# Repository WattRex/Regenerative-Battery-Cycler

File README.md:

<div style="display: flex; align-items: center;">
  
    <h1>TowerPower, a regenerative battery cycler</h1>
</div>

## The project

### Introduction

<p align="justify">The regenerative battery cycler is an innovative project aimed at providing a cost-effective, precise, and easy-to-build solution for testing batteries. It caters to a wide range of individuals and organizations, including researchers, R&D institutions, second life markets, and DIY energy enthusiasts who are interested in battery testing. The roots of this project trace back to 2018 when Pablo Pastor embarked on his PhD journey, focusing on machine learning for second life  batteries. During his research, he encountered a significant challenge: there was a scarcity of open-source aging databases. Determined to address this issue, Pastor and his team proposed creating  their own databases. However, due to budget constraints, they had to find an affordable solution. The initial concepts were developed within the Group of Power Electronics and Microelectronics (GEPM). </p>

<p align="justify">Over time, these concepts evolved, prioritizing three key factors: cost, simplicity, and precision. In 2021, a group of power electronic engineers, software developers, and energy sector experts from the PTI-Transener platform, operated by the Spanish National Research Council (CSIC) joined forces to propel the project forward. The team is currently focused on adapting the regenerative battery cycler to accommodate various battery chemistries, ensuring its versatility and applicability across different industries. </p>

<p align="justify">As part of the Pastor's thesis and the PTI-Transener project, we have made the decision to share the regenerative battery cycler as an open-source product. This approach aims to support other researchers and energy enthusiasts by providing them with a low-budget option for their studies. Additionally, we emphasize a structured development process, ensuring transparency and accountability. All steps, design decisions, and technical details, from initial system requirements to final schematics, bill of materials (BOM), and embedded code are openly shared, enabling others to replicate and build upon our work. </p>

<p align="justify">By providing a cost-effective, accessible, and open-source regenerative battery cycler: TowerPower. We aim to facilitate battery testing and contribute to the advancement of research and development in the field of energy storage. </p>

### Working principle

<p align="justify">TowerPower stands out as a bidirectional system, capable of both charging and discharging cells. This versatility allows for comprehensive testing and evaluation of batteries under various operating conditions. Moreover, unlike many low-end cyclers that dissipate energy as heat, TowerPower minimizes energy loss during the cycling process (taking into account system efficiency). By efficiently transferring energy from one battery to  another, this system proves to be significantly more economical to operate compared to chargers that rely on resistive discharging methods, which result in energy wastage. TowerPower optimizes energy utilization, ensuring a cost-effective and sustainable solution for battery testing and research. </p>

<p align="justify">TowerPower operates based on a DC-DC synchronous buck power converter, enabling energy transfer from a higher voltage input source to a lower voltage output where the device under test (DUT), such as a cell, is connected. The use of a buck converter allows control on the low voltage side while lacking control on the high voltage side, as seen in buck-boost converters. Moreover, the synchronous architecture of the converter enables bidirectional current flow, facilitating both charging and discharging processes. </p>

<p align="justify">To simplify the electronics and eliminate the need for energy transfer to the grid, the system uses an energy accumulator on the high voltage side. This can be achieved using a 12 V car battery or a stack of lithium cells with a voltage exceeding 5.5V. In our lab, a 6V high-capacity deep cycle gel Pb battery is used, allowing multiple cyclers to be connected in parallel. </p>

<p align="justify">The control of TowerPower is accomplished through a CAN bus interface, providing seamless communication between the cycler and the external controller. Additionally, a dedicated control software has been developed and released, enabling users to command test cycles and gather results effectively.  <a href="https://github.com/WattRex/Battery-Cyclers-Controler">Repo here</a>!</p>

<p align="justify">In this particular version of the cycler, a low-cost power device with integrated driver and transistors has been chosen. This decision not only reduces costs but also enhances the miniaturization of the product. Furthermore, the switching frequency of the converter has been increased, resulting in a smaller coil size, contributing to the overall cost and compactness of the system. </p>

### Acknowledgements
<p align="justify">This research has been developed within the CSIC Interdisciplinary Thematic Platform (PTI+) Transición Energética Sostenible+ (PTI-TRANSENER+) as part of the CSIC program for the Spanish Recovery, Transformation and Resilience Plan funded by the Recovery and Resilience Facility of the European Union, established by the Regulation (EU) 2020/2094. Funding from the Spanish Ministry of Science and Innovation under project MAFALDA (PID2021-126001OB-C32) is also acknowledged. </p>

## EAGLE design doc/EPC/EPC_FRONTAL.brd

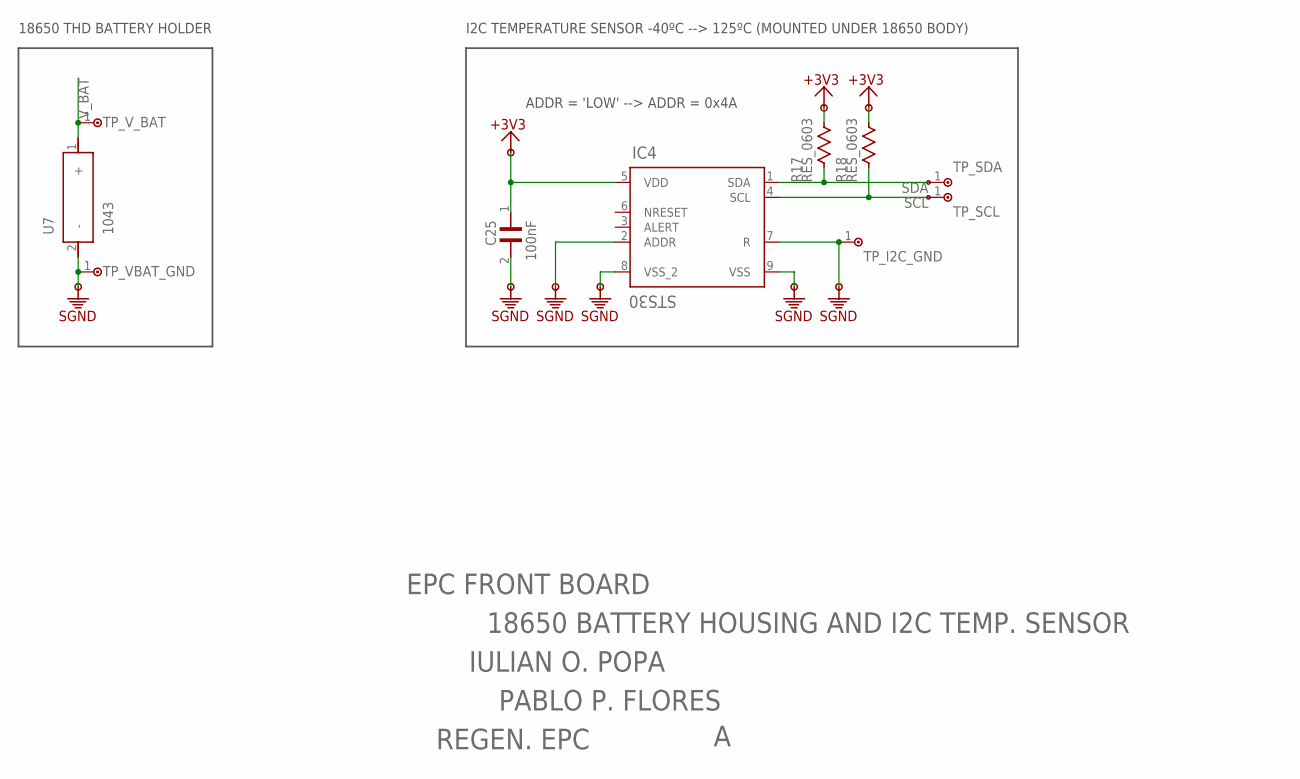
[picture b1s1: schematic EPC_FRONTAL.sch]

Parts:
C25: 100nF; CAP_0603
IC4: STS30; DFN
R17, R18: RES_0603
TP_I2C_GND: TP_S2751-46R
TP_SCL: TP_S2751-46R
TP_SDA: TP_S2751-46R
TP_VBAT_GND: TP_S2751-46R
TP_V_BAT: TP_S2751-46R
U7: 1043

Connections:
+3V3: C25.1, IC4.5 (VDD), R17.2, R18.2
SCL: IC4.4 (SCL), R18.1, TP_SCL.1
SDA: IC4.1 (SDA), R17.1, TP_SDA.1
SGND: C25.2, IC4.2 (ADDR), IC4.7 (R), IC4.8 (VSS_2), IC4.9 (VSS), TP_I2C_GND.1, TP_VBAT_GND.1, U7.2 (-)
V_BAT: TP_V_BAT.1, U7.1 (+)

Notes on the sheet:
ADDR = 'LOW' --> ADDR = 0x4A
18650 THD BATTERY HOLDER
I2C TEMPERATURE SENSOR -40ºC --> 125ºC (MOUNTED UNDER 18650 BODY)
EPC FRONT BOARD
18650 BATTERY HOUSING AND I2C TEMP. SENSOR
IULIAN O. POPA
PABLO P. FLORES
REGEN. EPC

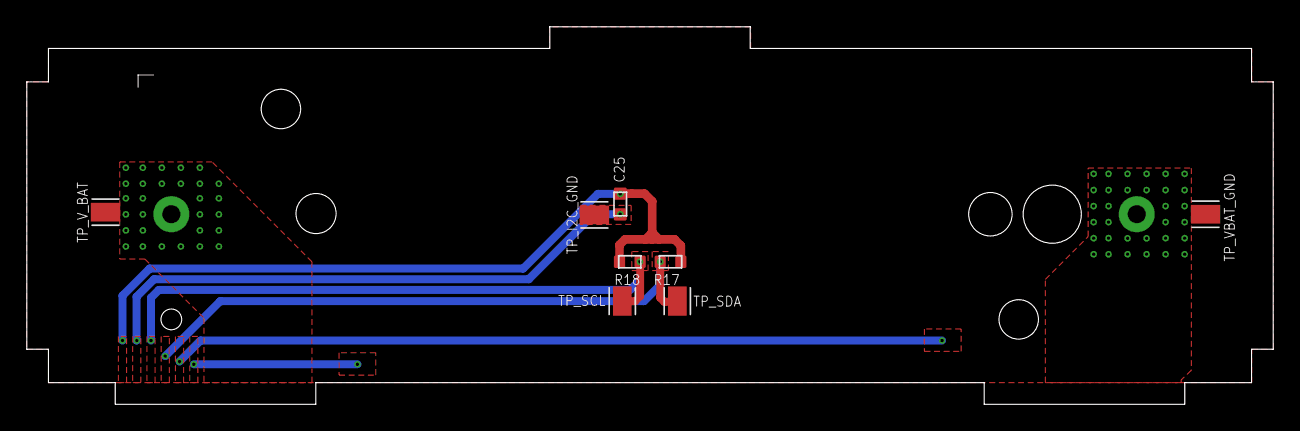
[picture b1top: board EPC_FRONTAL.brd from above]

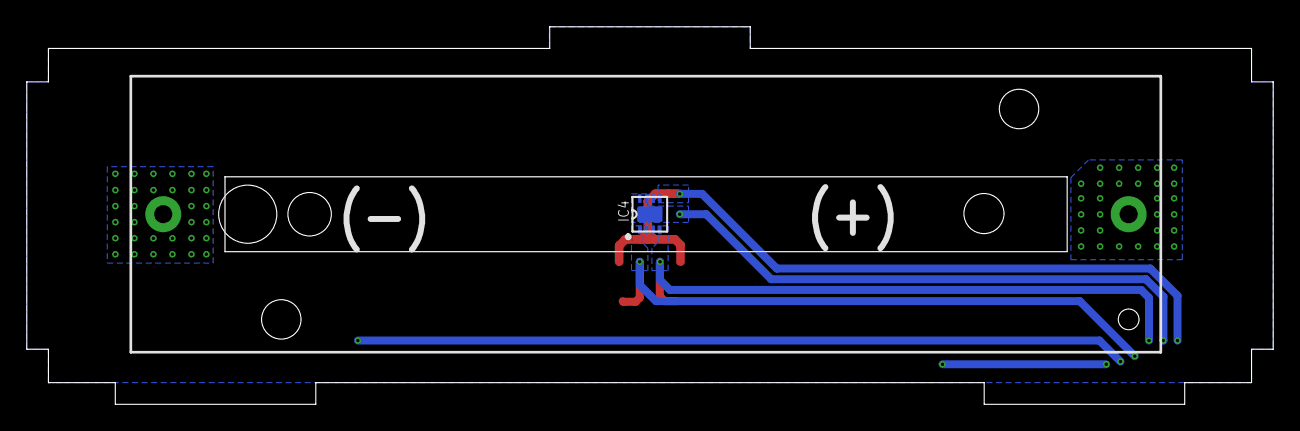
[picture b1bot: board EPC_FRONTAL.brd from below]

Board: 4 copper layers, 93.2 x 28.2 mm, 10 parts (2 on the bottom side), 5 nets.

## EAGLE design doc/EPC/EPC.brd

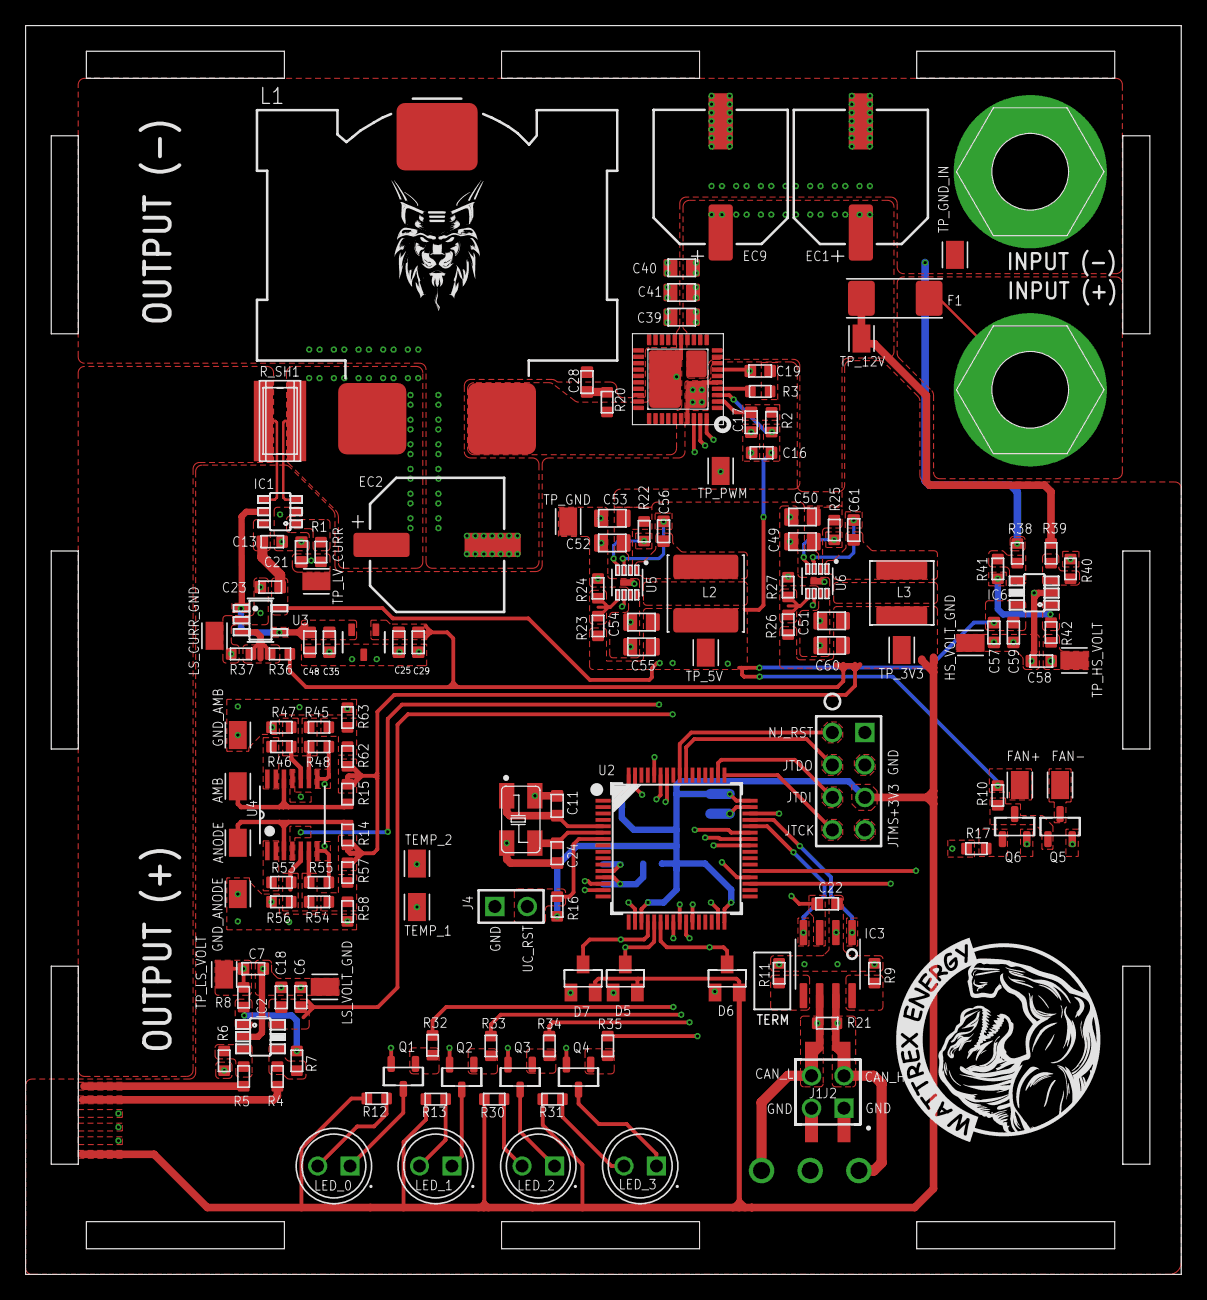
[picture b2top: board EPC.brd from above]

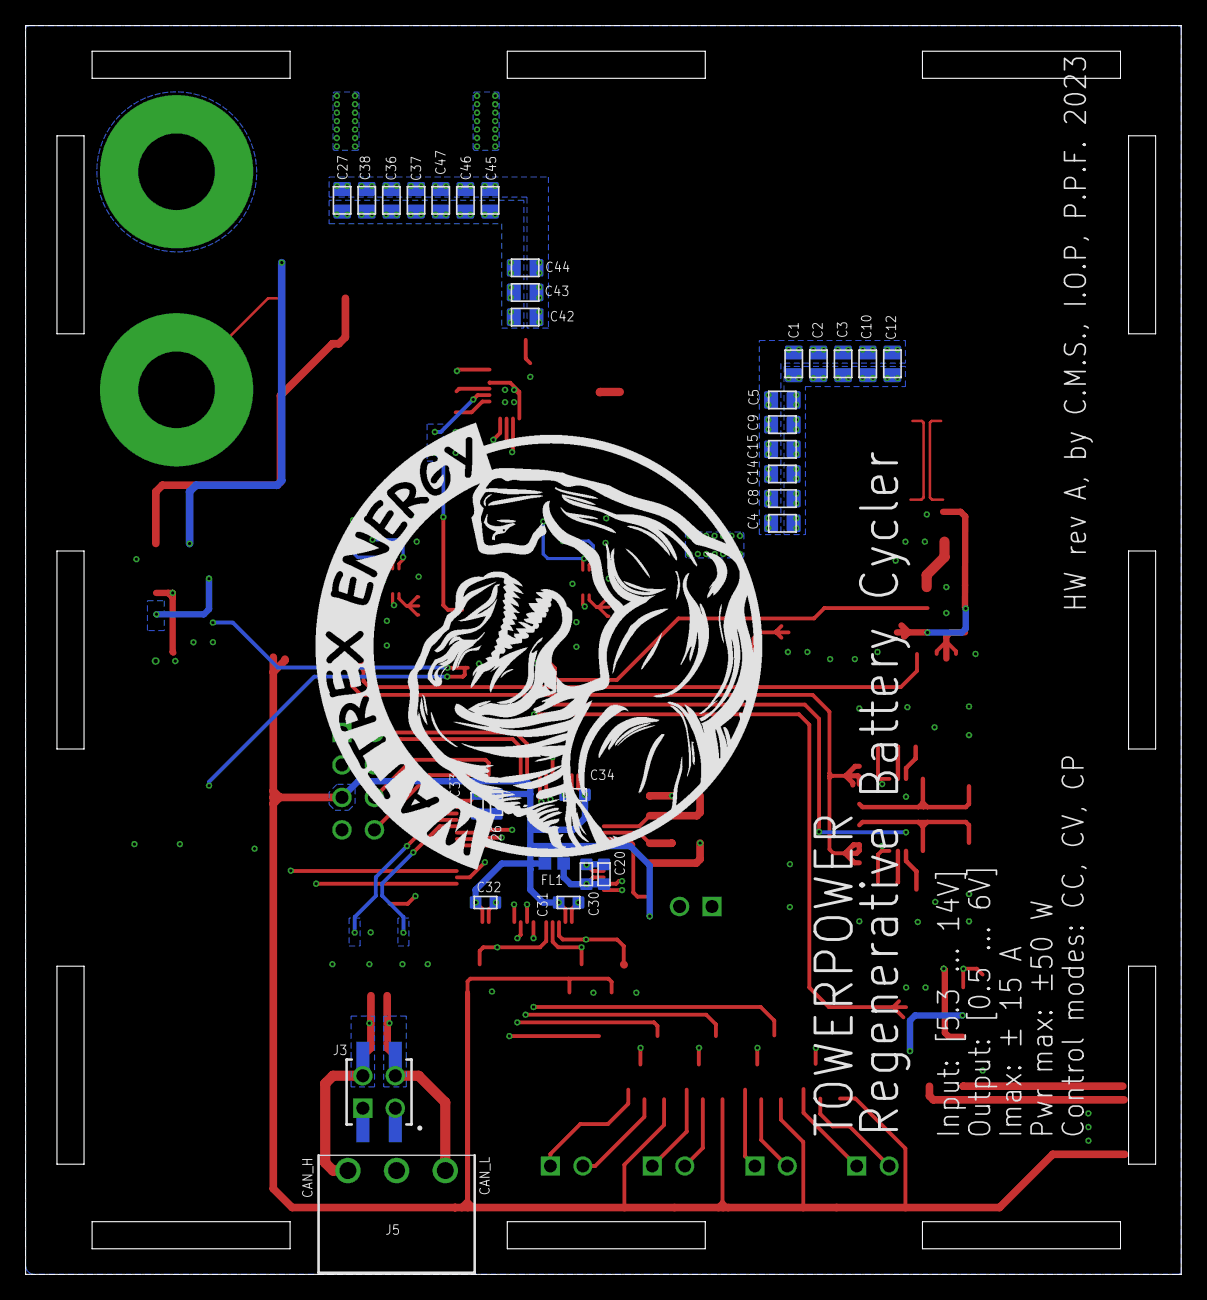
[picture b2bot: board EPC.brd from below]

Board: 4 copper layers, 90.5 x 97.8 mm, 174 parts (31 on the bottom side), 84 nets.

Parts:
AMB: TP_S2751-46R
ANODE: TP_S2751-46R
C1, C2, C3, C4, C5, C8, C9, C10, C12, C14, C15, C27, C36, C37, C38, C39, C40, C41, C42, C43, C44, C45, C46, C47, C51, C54, C55, C60: 22uF / 0805; CAP_0805
C6, C13, C19, C20, C22, C23, C25, C29, C31, C32, C33, C34, C35, C48, C57: 100nF; CAP_0603
C7, C21, C58: Cf; CAP_0603
C11, C24: 22pF; CAP_0603
C16, C17, C18, C30, C59: 1uF; CAP_0603
C26: 4.7uF; CAP_0603
C28: Csnb; CAP_0603
C49, C50, C52, C53: 10uF / 0805; CAP_0805
C56, C61: 10nF; CAP_0603
D5, D6, D7: BAT54S
EC1, EC2, EC9: 100uF; WCAP-PSLC_10X12.4(DXL)
F1: FUSE_SF-2410FP010T-2FUSE_SF_6P1X2P6_BRN-M; FUSE_SF-2410FP010T-2
FAN+: TP_S2751-46R
FAN-: TP_S2751-46R
FL1: 600Ohm/100MHz; FERR_0603_600OHM
GND_AMB: TP_S2751-46R
GND_ANODE: TP_S2751-46R
HS_VOLT_GND: TP_S2751-46R
IC1: INA181A2IDBVTDBV0006A_L; SOT-23-6
IC2, IC6: TSV7721ILT; SOT-23-5
IC3: MAX3059ASA
IC4: MAX6018AEUR16+T21-0051H_MXM-L; SOT-23
J1, J3: SSM-102-T-DV
J2: TSW-125-19-T-D
J4: 2_POS_HEADER
J5: CONN_3_POS
JTAG1: JTAG
L1: PQ2617BHA-150K
L2: VLS6045EX-220M; IND_VLS6045EX-220M
L3: VLS5045EX-150M; IND_VLS5045EX-150M
LED_0, LED_1, LED_2, LED_3: WP7113ID; LED_WP7113ID
LS_CURR_GND: TP_S2751-46R
LS_VOLT_GND: TP_S2751-46R
Q1, Q2, Q3, Q4, Q6: NX7002AK_215
Q5: PJA3430; NX7002AK_215
R1, R8, R42: Rf; RES_0603
R2: 10Ω; RES_0603
R3: 2Ω; RES_0603
R4, R5: 150kΩ; RES_0603
R6, R7: 82kΩ; RES_0603
R9: 51kΩ; RES_0603
R10, R16, R36, R37: 10kΩ; RES_0603
R11: R0; RES_0603
R12, R13, R17, R30, R31, R32, R33, R34, R35: 1kΩ; RES_0603
R14, R15: 3.32kΩ; RES_0603
R19: FCSL64R002GERRES_FCSL64_OHM-M; RES_FCSL64_OHM-M
R20: Rsnb; RES_0603
R21: 120Ω; RES_0603
R22, R25, R38, R39: 100kΩ; RES_0603
R23: 120kΩ; RES_0603
R24, R40, R41: 22kΩ; RES_0603
R26, R45, R46, R53, R54: 110kΩ; RES_0603
R27: 36kΩ; RES_0603
R47, R48, R55, R56: 140kΩ; RES_0603
R57, R62: 16.5kΩ; RES_0603
R58, R63: 2.2kΩ; RES_0603
R_SH1: WSL10203L000FEA; RES1020
SP1, SP2: SPACER_M6X25MM
TEMP_1, TEMP_2: TP_S2751-46R
TP_3V3, TP_5V, TP_12V: TP_S2751-46R
TP_GND: TP_S2751-46R
TP_GND_IN: TP_S2751-46R
TP_HS_VOLT: TP_S2751-46R
TP_LS_VOLT: TP_S2751-46R
TP_LV_CURR: TP_S2751-46R
TP_PWM: TP_S2751-46R
U1: FDMF6820C
U2: STM32F334R8T6; STM32F334R8
U3: TL071HIDBVR
U4: LM224APT
U5, U6: RT7251AZQW; WDFN-8L
XTAL1: MCSJK-7I-8.00-10-30-60-B-30

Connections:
+3V3: C25.1, C26.1, C29.1, C31.1, C32.1, C33.1, C34.1, C51.1, C60.1, D5.K, D6.K, D7.K, FL1.2, IC4.1, JTAG1.06, L3.2, R12.2, R13.2, R14.1, R15.1, R16.2, R26.2, R30.2, R31.2, R36.2, R57.2, R62.2, TP_3V3.1, U2.19, U2.32, U2.48, U2.64
+5V: C6.1, C13.1, C16.1, C18.1, C22.1, C23.1, C54.1, C55.1, C57.1, C59.1, FAN+.1, IC1.6, IC2.5, IC3.3, IC6.5, L2.2, R2.2, R10.2, R23.2, TP_5V.1, U1.3, U3.5, U4.4
+12V: C27.1, C36.1, C37.1, C38.1, C39.1, C40.1, C41.1, C42.1, C43.1, C44.1, C45.1, C46.1, C47.1, C49.1, C50.1, C52.1, C53.1, EC1.1, EC9.1, F1.2, R22.1, R25.1, R39.1, TP_12V.1, U1.9, U1.10, U1.11, U1.12, U1.13, U1.14, U1.42, U5.2, U6.2
CAN_H: IC3.7, J1.02, J2.02, J3.04, J5.1, R21.2
CAN_L: IC3.6, J1.04, J2.04, J3.02, J5.3, R21.1
CAN_RX: IC3.4, U2.44
CAN_TX: IC3.1, U2.45
EXT_TEMP_1: R55.1, TEMP_1.1, U2.15, U4.7
EXT_TEMP_2: R48.2, TEMP_2.1, U2.14, U4.8
FAN_CTRL: R17.1, U2.37
HS_VOLT: C58.1, D6.AK, R42.2, TP_HS_VOLT.1, U2.22
LED0: R32.1, U2.24
LED1: R33.1, U2.25
LED2: R34.1, U2.26
LED3: R35.1, U2.27
LS_CURR: C21.1, D7.AK, R1.2, TP_LV_CURR.1, U2.20
LS_VOLT: C7.1, D5.AK, R8.2, TP_LS_VOLT.1, U2.21
unnamed: IC1.1, R1.1
unnamed: C19.1, R3.2
unnamed: R3.1, U1.4
unnamed: IC2.4, R4.2, R7.1
unnamed: IC2.3, R5.2, R6.2
unnamed: IC2.1, R7.2, R8.1
unnamed: C28.1, R20.2
unnamed: Q5.1, Q6.3, R10.1
unnamed: FAN-.1, Q5.3
unnamed: IC6.4, R38.2, R41.1
unnamed: IC6.3, R39.2, R40.2
unnamed: IC6.1, R41.2, R42.1
unnamed: Q6.1, R17.2
unnamed: R25.2, U6.4
unnamed: C61.1, L3.1, U6.1
unnamed: R26.1, R27.2, U6.5
unnamed: C61.2, U6.3
unnamed: R22.2, U5.4
unnamed: C56.1, L2.1, U5.1
unnamed: R23.1, R24.2, U5.5
unnamed: C56.2, U5.3
unnamed: R45.1, R48.1, U4.9
unnamed: IC3.8, R9.2
unnamed: IC3.5, R11.2
unnamed: LED_0.A, R12.1
unnamed: LED_0.C, Q1.3
unnamed: LED_1.C, Q2.3
unnamed: LED_1.A, R13.1
unnamed: LED_2.A, R30.1
unnamed: LED_2.C, Q3.3
unnamed: LED_3.C, Q4.3
unnamed: LED_3.A, R31.1
unnamed: Q1.1, R32.2
unnamed: R46.2, R47.2, U4.10
unnamed: Q2.1, R33.2
unnamed: Q3.1, R34.2
unnamed: Q4.1, R35.2
unnamed: R36.1, R37.2, U3.3
unnamed: F1.1, SP1.P$1
unnamed: R53.1, R56.1, U4.5
unnamed: R54.2, R55.2, U4.6
unnamed: R54.1, R57.1, R58.2
unnamed: R45.2, R62.1, R63.2
NTC_1: ANODE.1, R14.2, U4.3
NTC_2: AMB.1, R15.2, U4.12
OUT_DISABLE: U1.39, U2.42
PWM_OUT: TP_PWM.1, U1.40, U2.41
RCC_OSC_IN: C11.1, U2.5, XTAL1.#1
RCC_OSC_OUT: C24.1, U2.6, XTAL1.#3
REF_1V65: C35.1, C48.1, IC1.5, IC4.2, U3.1, U3.4
SGND: C1.2, C2.2, C3.2, C4.2, C5.2, C6.2, C7.2, C8.2, C9.2, C10.2, C11.2, C12.2, C13.2, C14.2, C15.2, C16.2, C17.2, C18.2, C20.2, C21.2, C22.2, C23.2, C24.2, C25.2, C26.2, C27.2, C28.2, C29.2, C30.2, C31.2, C32.2, C33.2, C34.2, C35.2, C36.2, C37.2, C38.2, C39.2, C40.2, C41.2, C42.2, C43.2, C44.2, C45.2, C46.2, C47.2, C48.2, C49.2, C50.2, C51.2, C52.2, C53.2, C54.2, C55.2, C57.2, C58.2, C59.2, C60.2, D5.A, D6.A, D7.A, EC1.2, EC2.2, EC9.2, GND_AMB.1, GND_ANODE.1, HS_VOLT_GND.1, IC1.2, IC2.2, IC3.2, IC4.3, IC6.2, J1.01, J1.03, J2.01, J2.03, J3.01, J3.03, J4.01, J5.2, JTAG1.07, LS_CURR_GND.1, LS_VOLT_GND.1, Q1.2, Q2.2, Q3.2, Q4.2, Q5.2, Q6.2, R4.1, R6.1, R9.1, R11.1, R24.1, R27.1, R37.1, R38.1, R40.1, R47.1, R56.2, R58.1, R63.1, SP2.P$1, TP_GND.1, TP_GND_IN.1, U1.5, U1.16, U1.17, U1.18, U1.19, U1.20, U1.21, U1.22, U1.23, U1.24, U1.25, U1.26, U1.27, U1.28, U1.37, U1.41, U2.12, U2.18, U2.31, U2.47, U2.60, U2.63, U3.2, U4.11, U5.7, U5.8, U5.9, U6.7, U6.8, U6.9, XTAL1.GND, XTAL1.GND_2
STATUS_3V3: U2.35, U6.6
STATUS_5V0: U2.36, U5.6
SW: C19.2, L1.2, R20.1, U1.7, U1.15, U1.29, U1.30, U1.31, U1.32, U1.33, U1.34, U1.35, U1.43
SYS_JTCK-SWCLK: JTAG1.04, U2.49
SYS_JTDI: JTAG1.03, U2.50
SYS_JTDO-TRACESWO: JTAG1.02, U2.55
SYS_JTMS-SWDIO: JTAG1.05, U2.46
SYS_NJTRST: JTAG1.01, U2.56
THERMAL_WARN: U1.38, U2.43
T_AMP_1_OUT_1: R53.2, U4.1, U4.2
T_AMP_1_OUT_4: R46.1, U4.13, U4.14
UC_NRST: J4.02, R16.1, U2.7
VCIN: C17.1, R2.1, U1.2
VDDA: C20.1, C30.1, FL1.1, U2.13
V_BAT: IC1.4, R5.1, R19.2, R_SH1.2
V_OUT: C1.1, C2.1, C3.1, C4.1, C5.1, C8.1, C9.1, C10.1, C12.1, C14.1, C15.1, EC2.1, IC1.3, L1.1, R19.1, R_SH1.1

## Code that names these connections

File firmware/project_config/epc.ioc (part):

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Mcu.Name=STM32F334R(6-8)Tx
Mcu.Package=LQFP64
Mcu.UserName=STM32F334R8Tx
PA0.GPIOParameters=GPIO_Label
PA0.GPIO_Label=Ext_Temp_2
PA0.Mode=IN1-Single-Ended
PA0.Signal=ADC1_IN1
PA1.GPIOParameters=GPIO_Label
PA1.GPIO_Label=Ext_Temp_1
PA1.Mode=IN2-Single-Ended
PA1.Signal=ADC1_IN2
PA10.GPIOParameters=GPIO_Label
PA10.GPIO_Label=Thermal_Warn 
PA10.Signal=GPIO_Input
PA11.Mode=CAN_Activate
PA11.Signal=CAN_RX
PA12.Mode=CAN_Activate
PA12.Signal=CAN_TX
PA13.Mode=JTAG_5_pins
PA13.Signal=SYS_JTMS-SWDIO
PA14.Mode=JTAG_5_pins
PA14.Signal=SYS_JTCK-SWCLK
PA15.Mode=JTAG_5_pins
PA15.Signal=SYS_JTDI
PA4.GPIOParameters=GPIO_Label
PA4.GPIO_Label=Ls_Curr 
PA4.Mode=IN1-Single-Ended
PA4.Signal=ADC2_IN1
PA5.GPIOParameters=GPIO_Label
PA5.GPIO_Label=Ls_Volt 
PA5.Mode=IN2-Single-Ended
PA5.Signal=ADC2_IN2
PA6.GPIOParameters=GPIO_Label
PA6.GPIO_Label=Hs_Volt
PA6.Mode=IN3-Single-Ended
PA6.Signal=ADC2_IN3
PA8.GPIOParameters=GPIO_Label
PA8.GPIO_Label=Pwm_Out
PA8.Mode=Output_TA1
PA8.Signal=HRTIM1_CHA1
PA9.GPIOParameters=GPIO_PuPd,GPIO_Label,GPIO_ModeDefaultOutputPP
PA9.GPIO_Label=Out_Disable 
PA9.GPIO_ModeDefaultOutputPP=GPIO_MODE_OUTPUT_PP
PA9.GPIO_PuPd=GPIO_NOPULL
PA9.Signal=GPIO_Output
PB0.GPIOParameters=GPIO_Label
PB0.GPIO_Label=Led2
PB0.Signal=GPIO_Output
PB1.GPIOParameters=GPIO_Label
PB1.GPIO_Label=Led3
PB1.Signal=GPIO_Output
PB14.GPIOParameters=GPIO_Label
PB14.GPIO_Label=Status_3v3
PB14.Signal=GPIO_Input
PB15.GPIOParameters=GPIO_Label
PB15.GPIO_Label=Status_5v0
PB15.Signal=GPIO_Input
PB3.Mode=JTAG_5_pins
PB3.Signal=SYS_JTDO-TRACESWO
PB4.Mode=JTAG_5_pins
PB4.Signal=SYS_NJTRST
PB6.GPIOParameters=GPIO_Label
PB6.GPIO_Label=SCL
PB6.Mode=I2C
PB6.Signal=I2C1_SCL
PB7.GPIOParameters=GPIO_Label
PB7.GPIO_Label=SDA
PB7.Mode=I2C
PB7.Signal=I2C1_SDA
PC4.GPIOParameters=GPIO_Label
PC4.GPIO_Label=Led0
PC4.Signal=GPIO_Output
PC5.GPIOParameters=GPIO_Label
PC5.GPIO_Label=Led1
PC5.Signal=GPIO_Output
PF0\ /\ OSC_IN.Mode=HSE-External-Oscillator
PF0\ /\ OSC_IN.Signal=RCC_OSC_IN
PF1\ /\ OSC_OUT.Mode=HSE-External-Oscillator
PF1\ /\ OSC_OUT.Signal=RCC_OSC_OUT
RCC.HSEPLLFreq_Value=8000000
RCC.HSE_VALUE=8000000
RCC.SYSCLKFreq_VALUE=72000000
RCC.SYSCLKSourceVirtual=RCC_SYSCLKSOURCE_PLLCLK
board=custom

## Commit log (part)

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2023-05-23 Added .gitignore
2023-05-23 HAL and MID sw arch partially designed
2023-05-24 Minor changes
2023-05-24 Added STM project config gitignore
2023-05-24 Add project configuration for STM32CubeIDE and STM32CubeMX
2023-05-24 Gitignore: no debug and release forlder
2023-05-29 Main project and readme ready
2023-05-29 Add skeleton files for system init
2023-05-29 initial configuration clarification added to README
2023-05-29 Deleted source location folder and add app_salg and hal_sys
2023-05-29 Add feature HAL_GPIO functional
2023-05-29 Add feature HAL_CAN not receiving
2023-05-30 Fix problem in init function and add test functions
2023-05-30 Add readme in hal gpio for test instructions
2023-05-30 Add test structure
2023-05-30 Include Test folder
2023-05-30 Move test files
2023-05-30 Naming conv and all test performs on test folder
2023-05-30 Relocated and rename of readme for gpio test
2023-05-30 Add doc
2023-05-30 Changes in headers of files
2023-05-30 Change wwdg to iwdg
2023-05-30 Mafalda ackg added to README.md
2023-05-30 Add Test files for CAN
2023-05-31 Add filter
2023-05-31 Minor changes: add const and nc
2023-05-31 headers and naming convention fixed. Includes needed in .c changed from .h to .c
2023-05-31 variable naming error fixed
2023-05-31 headers changed. deleted non needed includes and sections of code
2023-05-31 Add filterMask configuration and test functions, solve mistakes with pointers
2023-05-31 Change headers of HAL files
2023-05-31 Timers working
2023-05-31 Deleted old headers
2023-06-01 Watchdog working, reset after 0.5 ms
2023-06-01 Integrated tests for IWDG
2023-06-01 Removed public test function
2023-06-01 Made callback RT timer public on test timer
2023-06-01 Add robustness to HAL_TmrGetTicks
2023-06-01 Change module to HAL_SDS, module able to read temperature from sensor
2023-06-02 Final name for HAL fully operational
2023-06-02 Minor changes and corrections
2023-06-02 Change all necesary names containing i2c to sts
2023-06-02 Minor changes in names
2023-06-02 Add readme for tmr test, with previous actions
2023-06-02 leds status machine logic added
2023-06-02 Add changes request for pull request
2023-06-05 epc_str_err definition to fix error_handler in ST HAL
2023-06-05 epc_str_err used to fix error_handler in main
2023-06-05 epc_str_err used to fix error_handler in HAL_CAN
2023-06-05 epc_str_err used to fix error_handler in HAL_SYS
2023-06-05 epc_str_err used to fix error_handler in HAL_GPIO
2023-06-05 epc_str_err used to fix error_handler in HAL_WDG
2023-06-05 Change path epc_st
2023-06-05 Change errors names and includes as suggested in pull request
2023-06-05 Add pwm config
2023-06-06 Minor changes in test
2023-06-06 registers structures definition added
2023-06-06 MID_DABS leds conf and first version of MID_REG added
2023-06-06 MID_REG class diagram updated
2023-06-06 MID_REG strucs definition and extern variables initialization
2023-06-06 included extern definition of global variable EPC_ST_ERR_COUNTER where is used
2023-06-06 Done changes suggested in pull request
2023-06-07 MID_REG provided IF changed. MID_DABS functions completed
2023-06-07 First version of mid dabs, partially done but not tested, final interface not define yet
2023-06-07 deleted non used initializations
2023-06-07 Add some comments to functions
2023-06-07 ADC1&2 working with DMA and timer 2 and 3
2023-06-07 Integrate ADC and DMA
2023-06-07 Project config for ADC and DMA
2023-06-08 registers initializations in EPC_CONF
2023-06-08 registers and defines initialization in EPC_CONF
2023-06-08 registers initialization in APP_SALG
2023-06-08 Fix errors on MID_PWR
2023-06-08 initialization and definition of registers in APP_IFACE
2023-06-08 Update hal_adc Callbacks
2023-06-08 Change DMA cplt callback
2023-06-08 Update temp enums ADC
2023-06-08 Update hal_adc with new enum for temp
2023-06-09 First approach to mid pwr
2023-06-12 MID_REG_meas_s type changed to MID_REG_meas_property_s
2023-06-12 First approach of HAL_SYS
2023-06-13 Update in pwm and pwr
2023-06-13 minor change
2023-06-13 Add error priority in led status
2023-06-13 Error in update meas solve
2023-06-13 Solve naming convention with EPC_CONF_info
2023-06-13 Update configuration from excel and naming convention
2023-06-15 Update in function descriptions
2023-06-15 Minor change in includes
2023-06-15 Changes on MID_COMM and APP_IFACE
2023-06-16 Added test files
2023-06-16 Send functions tested and working, callback not tested
2023-06-16 Update interface of HAL_GPIO
2023-06-16 Integrated tests for MID_COMM
2023-06-16 Update measure conversion to Y=x*factor + offset
2023-06-19 Change math operation to factors + offset registers imported from epc_conf
2023-06-19 Add function AddFilters and DelFilters
2023-06-19 Update HAL_ADC
2023-06-19 Update HAL_STS
2023-06-19 Update HAL_WDG
2023-06-19 Update HAL_TMR
2023-06-19 Update MID_REG
2023-06-19 Update EPC_CONF & MID_DABS
2023-06-19 APP_CtrlUpdate structure added
2023-06-19 Update MID_PWR
2023-06-20 Minor changes for naming convention
2023-06-20 Update MID_PWR with mapping definitions
2023-06-20 Update HAL_SYS
2023-06-20 Update MID_COMM
2023-06-20 APP_CTRL added
2023-06-20 APP_CTRL integrated with MID_PWR calls. Not tested
2023-06-20 pointer added to call
2023-06-20 Added registers for measure conversion and first approach to Kpid for pwr control
2023-06-20 APP_CTRL updated
2023-06-20 MID_REG_errorStatus_s changed to MID_REG_error_status_s
2023-06-20 Update names to match last changes in mid_reg with naming convention
2023-06-20 Added explanation to functions
2023-06-20 Change names in .c and added defines for test in .h
2023-06-20 APP_CtrlApplyNewMode activity diagram added
2023-06-21 Update periodic messages struct
2023-06-21 Change periodic struct in MID_REG
2023-06-21 fixed error in DelFilters
2023-06-21 Minor change in name
2023-06-21 Update comm test and finish development of comm
2023-06-21 Add implementation of fixed point representation
2023-06-21 Added conversion to deci units
2023-06-21 Minor changes, declaration internal functions
2023-06-21 APP_CtrlUpdate action diagram added
2023-06-21 Update registers of MID_REG
2023-06-21 Pending TODO solved
2023-06-22 Implement executive cycling on salg
2023-06-23 Naming convention
2023-06-23 Minor changes in constant
2023-06-23 First version of APP_IFACE
2023-06-23 mean of 3 medians
2023-06-26 Update, m% deleted, now the setDuty works with values between min duty and HAL_PWM_period -1
2023-06-26 Test required changes from last update
2023-06-26 Minor changes in d0 function
2023-06-26 Changes in MID_PWR
2023-06-26 Added activity flow of HAL_PWM and STS
2023-06-26 Update Activity diagram HAL_STS, HAL_GPIO, HAL_CAN
2023-06-27 Change control, now PI current calculates deltaDuty to add to d0; minor changes
2023-06-27 Update with changes from MID_PWR interface
2023-06-27 Requested changes, solved multiplication by decimals in test
2023-06-27 Changes in defines in Kpi for pwr, and order in measurements
2023-06-27 Changes for HRTIM, update duty to apply at the beginning of the next period
2023-06-27 Minor change, missing definition
2023-06-27 Order of limits in epc_conf, (V_LS,C_LS,v_HS,PWR,T)(MAX,MIN)
2023-06-27 Electrical cad added
2023-06-28 Solved error in ADC
2023-06-28 Update for pwr control
2023-06-28 Add comments to code for pwr
2023-06-28 Update minor changes and with comments in code
2023-06-29 Update init, to add filters with epc_conf_info id + pcanviewer example messages to transmit
2023-06-29 Update register periodic time min and CAN ID
2023-06-29 Update values for measurements, now there is values for test board and final release
2023-06-30 Added constant to function arguments, comments on enums
2023-06-30 Added const to arguments of callbacks, added comments
2023-06-30 Fixed condition in TmrDelay
2023-06-30 Deleted test values
2023-06-30 Update activity diagram HAL_ADC
2023-06-30 Update definition for magic number MIN_PWM
2023-06-30 Update control, d0 calculated just first time avoiding current peak
2023-06-30 Update activity flow HAL_SYS
2023-06-30 Update timing diagram
2023-07-10 Minor change, order in enums to match specifications
2023-07-10 Minor changes for improvement, added code to satisfy specifications
2023-07-10 Update order in enums and default test messages for pcanViewer
2023-07-10 Update leds to move as the current
2023-07-10 Completing updates from last commit
2023-07-10 Minor changes to make it work correctly with all the code
2023-07-10 Update SALG to make it work with all the code, improvement in code and added comments
2023-07-10 Update current conversion for final boards
2023-07-10 Update activity diagram salg
2023-07-10 Minor changes, deleted commented lines
2023-07-10 Activity mid pwr
2023-07-10 Activity mid dabs
2023-07-13 Fixed periodic messages, now available both measures elect and temp
2023-07-13 Updated with app_iface and mid_comm activity diagram
2023-07-13 change in leds for hs and ls volt error
2023-07-20 Added hyperperiod for updating temperature measures
2023-07-20 Forgot define hyperperiod temperatures
2023-07-20 Changes to init sts only if the hardware version has it
2023-07-20 Update temperature conversion values and change i2c configuration to go faster up to 1MHz, previously 200kHz
2023-07-21 Update to read from temperature sensors if the hardware is installed
2023-07-21 Added struc and enums for hardware versions infor
2023-07-21 Update code to ignore messages that change mode, consigns or limits
2023-07-21 Update init with hw version register for sts
2023-07-21 Update in hw_version register
2023-07-21 Update checkerrors to check only if sensor is present
2023-07-21 Update with hw_version registers and enums
2023-07-28 Added look up table for NTC temp sensors
2023-07-28 Added adc to temp conversion using look up table
2023-07-31 Added mid dabs init
2023-07-31 LICENSE comment added
2023-07-31 Brief in headers updated. License updated
2023-08-01 Add to send the change of the error status every 1 second if changed from previous
2023-08-01 Added MID_DabsInit to initilize specific variables
2023-08-01 Include defines fow hw versions
2023-08-01 Send error status if any error raised or unraised
2023-08-01 Error changing .h file with data in .c
2023-08-01 Minor change to make it work in dabs init
2023-08-01 Is not steps in ledMode is step
2023-08-02 Change position of leds for curr error and temp error
2023-08-02 Minor change, wrong temperature variable checking limits
2023-08-04 Minor change, now verifies both elect and temp periodic status
2023-08-04 Update app_iface.c check both meas periodic status
2023-08-04 minor change in epc conf comments
2023-08-07 Change in hw version initilization if there is STS sensor
2023-08-07 Deleted struct for hw and added directly to epc info
2023-08-07 Done TODO
2023-08-07 Change check epc info for temperature sensors
2023-08-07 Change hw version to check if there are temperature sensors
2023-08-07 Deleted hw version struct and added directly to epc conf info
2023-08-10 Ignore limits while trasitory
2023-08-10 Update epc_conf.h to include period or transitory
2023-08-10 Update SOA units
2023-08-10 limit check bug solved
2023-08-10 transcient time without limit checking in power and current limits
2023-08-11 Minor change to work properly the bitfield
2023-08-11 Change register to avoid wrong padding
2023-08-11 Change minor bugs in period ack
2023-08-11 Minor change in limit time
2023-08-16 Transition time changed
2023-08-16 fixed app_ctrl.c
2023-08-18 ignore wiki folder
2023-08-23 diagrams file name changed
2023-08-23 Add stm imports
2023-08-24 deleted mid_reg.h import from hal_adc. Not needed
2023-08-24 version code of hal_can.h changed
2023-08-24 version dates changed
2023-08-24 Minor change, wait mode only acepts time limit
2023-08-24 changed <stdint.h> in hal_tmr.h
2023-08-24 <stdint.h> in hal_wdg.h
2023-08-24 low level HAL STM correlations reviewed
2023-08-24 MID_COMM <stdint.h> import
2023-08-24 MID_COMM sw version
2023-08-24 connections added in components diagram
2023-08-27 components diagram finished. Exported to svg
2023-09-15 Hardware project files

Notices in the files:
parts and their libraries:
COPYRIGHT: Copyright (C) 2022 Ultra Librarian. All rights reserved.
COPYRIGHT: Copyright (C) 2023 Ultra Librarian. All rights reserved.
